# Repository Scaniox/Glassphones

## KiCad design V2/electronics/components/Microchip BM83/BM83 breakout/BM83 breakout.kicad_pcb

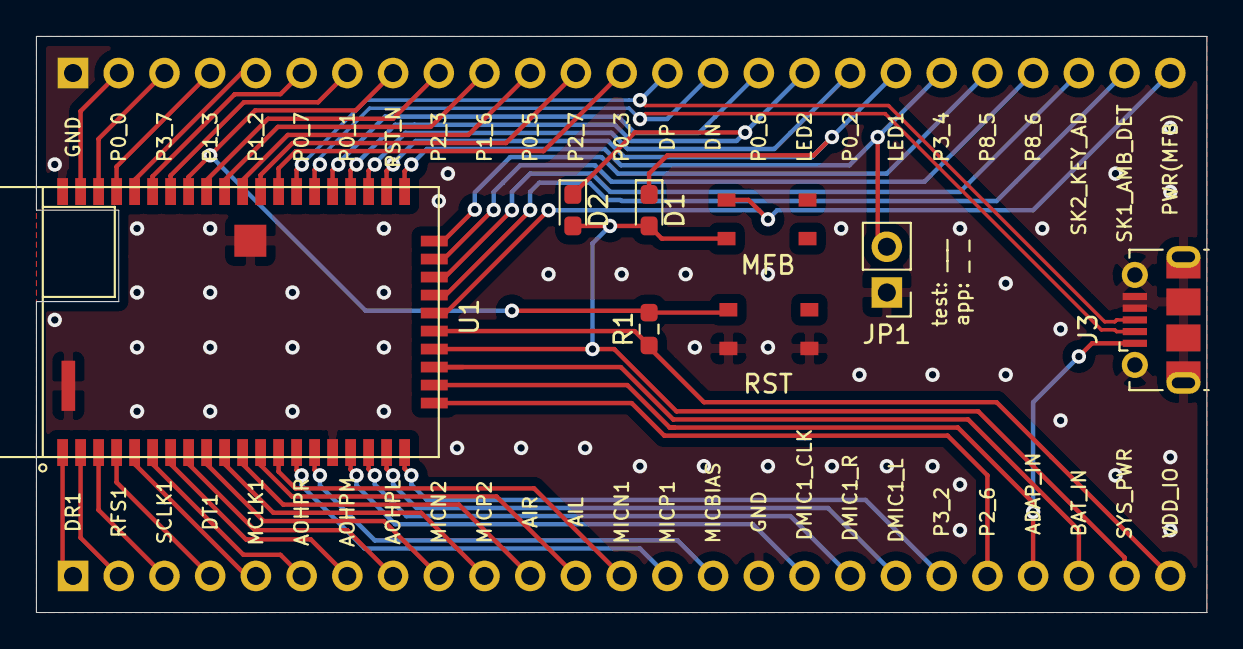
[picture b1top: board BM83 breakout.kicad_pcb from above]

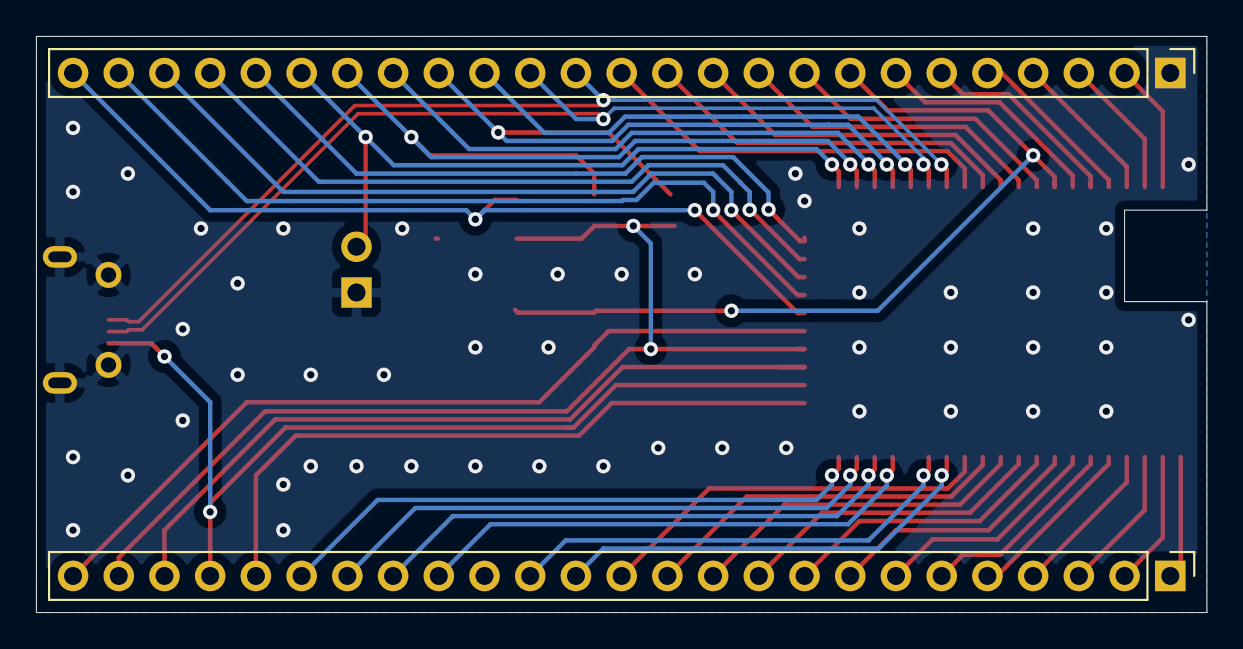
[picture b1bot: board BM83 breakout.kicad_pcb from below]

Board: 2 copper layers, 65.0 x 32.0 mm, 10 parts (2 on the bottom side), 49 nets.

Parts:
D1: LED1; LED_0603_1608Metric_Pad1.05x0.95mm_HandSolder
D2: LED2; LED_0603_1608Metric_Pad1.05x0.95mm_HandSolder
J1, J2: Conn_01x25; PinHeader_1x25_P2.54mm_Vertical
J3: USB_B_Micro; USB_Micro-B_Molex-105017-0001
JP1: Jumper_NO_Small; PinHeader_1x02_P2.54mm_Vertical
MFB: PWR MFB; TL3365_button
R1: 4R7; R_0603_1608Metric_Pad0.98x0.95mm_HandSolder
RST: RESET; TL3365_button
U1: BM83

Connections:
/ADAP_IN: J1.22, J3.1, U1.22
/AIL: J1.12, U1.12
/AIR: J1.11, U1.11
/AOHPL: J1.8, U1.8
/AOHPM: J1.7, U1.7
/AOHPR: J1.6, U1.6
/BAT_IN: J1.23, U1.23
/DMIC1_CLK: J1.17, U1.17
/DMIC1_L: J1.19, U1.19
/DMIC1_R: J1.18, U1.18
/DN: J2.15, J3.2, U1.36
/DP: J2.14, J3.3, U1.37
/DR1: J1.1, U1.1
/DT1: J1.4, U1.4
/LED1: D1.1, J2.19, U1.32
/LED2: D2.1, J2.17, U1.34
/MCLK1: J1.5, U1.5
/MICBIAS: J1.15, U1.15
/MICN1: J1.13, U1.13
/MICN2: J1.9, U1.9
/MICP1: J1.14, U1.14
/MICP2: J1.10, U1.10
/P0_0: J2.2, U1.49
/P0_1: J2.7, U1.44
/P0_2: J2.18, U1.33
/P0_3: J2.13, U1.38
/P0_5: J2.11, U1.40
/P0_6: J2.16, U1.35
/P0_7: J2.6, U1.45
/P1_2: J2.5, U1.46
/P1_3: J2.4, U1.47
/P1_6: J2.10, U1.41
/P2_3: J2.9, U1.42
/P2_6: J1.21, U1.21
/P2_7: J2.12, U1.39
/P3_2: J1.20, U1.20
/P3_4: J2.20, JP1.2, U1.31
/P3_7: J2.3, U1.48
/P8_5: J2.21, U1.30
/P8_6: J2.22, U1.29
/PWR(MFB): J2.25, MFB.1, U1.26
/RFS1: J1.2, U1.2
/RST_N: J2.8, R1.2, RST.2, U1.43
/SCLK1: J1.3, U1.3
/SK1_AMB_DET: J2.24, U1.27
/SK2_KEY_AD: J2.23, U1.28
/SYS_PWR: D1.2, D2.2, J1.24, MFB.2, U1.24
/VDD_IO: J1.25, R1.1, U1.25
GND: J1.16, J2.1, J3.4, J3.5, J3.6, JP1.1, RST.1, U1.16, U1.50

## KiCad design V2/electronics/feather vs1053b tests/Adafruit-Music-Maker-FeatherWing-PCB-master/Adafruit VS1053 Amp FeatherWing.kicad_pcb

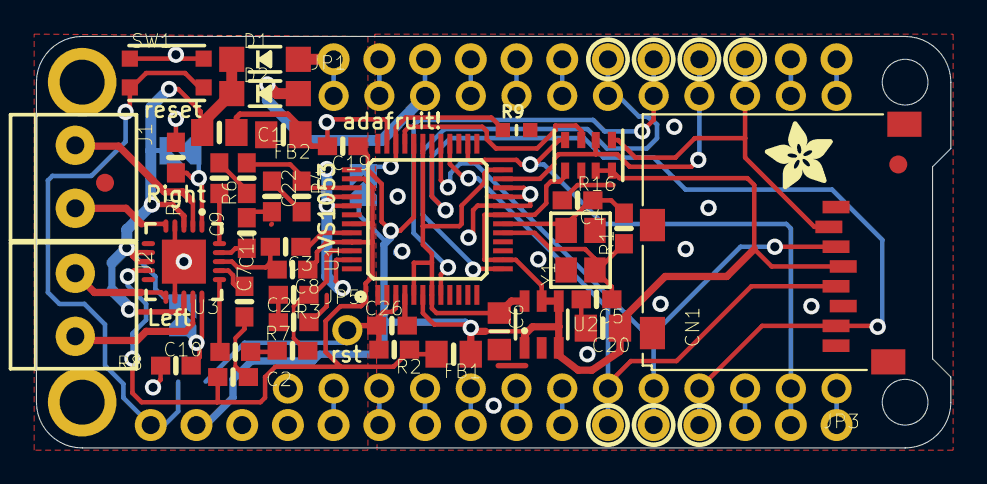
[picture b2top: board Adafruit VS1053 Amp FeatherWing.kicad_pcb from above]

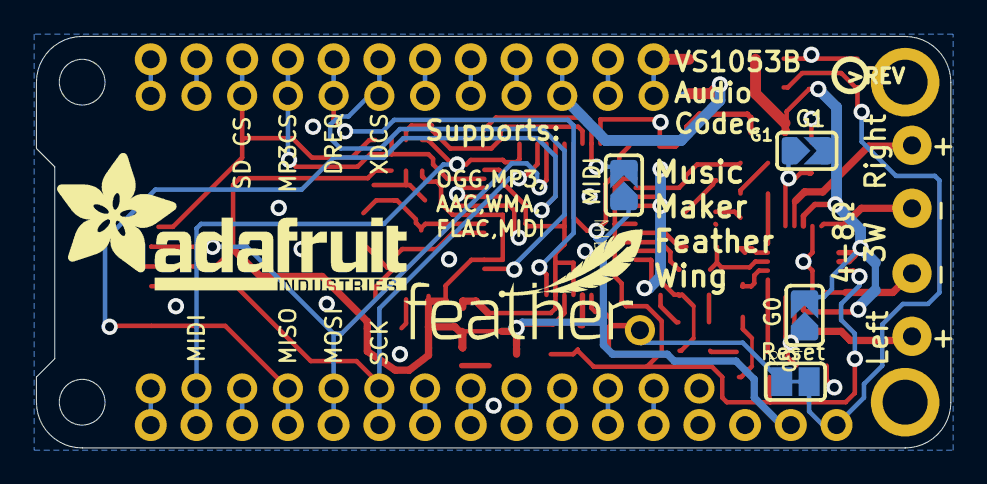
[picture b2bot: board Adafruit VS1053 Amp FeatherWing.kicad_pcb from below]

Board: 2 copper layers, 50.8 x 22.9 mm, 52 parts (7 on the bottom side), 53 nets.

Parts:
C1, C20: 10µF; 0805-NO
C2, C8, C26: 0.1µF; 0603-NO
C3: 1uF; 0603-NO
C4, C5: 22pF; 0603-NO
C6: 10µF; _0805MP
C7, C9, C10, C11, C19: 1µF; 0603-NO
C21, C22: 10nF; 0603-NO
CN1: 2908-05WB-M6; MICROSD
D1, D2: MBR120; SOD-123
FB1, FB2: FERITTE; 0805-NO
FID1, FID2: FIDUCIAL""; FIDUCIAL_1MM
G0, G1: SOLDERJUMPER_ARROW_NOPASTE
J1, J2: 3.5mm; TERMBLOCK_1X2-3.5MM
JP1: 1X12_ROUND
JP3: 1X13_ROUND_70
JP5: 1X01_ROUND
MIDI: SOLDERJUMPER_ARROW_NOPASTE
MS1: FEATHERWING_NODIM
R1: 1M; 0603-NO
R2, R5, R8: 100K; 0603-NO
R3, R4: 22; 0603-NO
R6, R7: 100; 0603-NO
R9: 100K; _0603MP
R16: 100K; RESPACK_4X0603
RST: SOLDERJUMPER_CLOSEDWIRE
SW1: KMR2; BTN_KMR2_4.6X2.8
U1: VS1053B; LQFP48
U2: AP7312-1833W6-7; SOT23-6
U3: TPA2012; WQFN20
U$36: ADAFRUIT_3.5MM
U$37: FEATHERLOGO_SMALL
U$43: PCBFEAT-REV-040
U$55: ADAFRUIT_TEXT_20MM
Y1: ABM8G-12.288MHZ-4Y-T3; CRYSTAL_3.2X2.5

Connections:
1.8V: C6.1, U1.5, U1.7, U1.24, U1.31, U2.6
3.3V: C19.1, C20.1, CN1.4, FB1.1, MIDI.1, MS1.2, R16.5, R16.7, R16.8, U1.6, U1.14, U1.19, U1.32, U2.1, U2.3, U2.4, U2.5
A: JP3.12, MS1.5
AGND: C2.2, C3.2, C7.1, C8.2, C11.1, C21.2, C22.2, FB2.2, U1.37, U1.40, U1.41, U1.47, U3.18
AVDD: C2.1, C8.1, FB1.2, R2.1, U1.38, U1.43, U1.45, U3.9
B: JP3.11, MS1.6
C: JP3.10, MS1.7
D: JP3.9, MS1.8
DREQ: JP1.8, MS1.21, U1.8
E: JP3.8, MS1.9
EN: JP1.2, MS1.27
F: JP3.7, MS1.10
G: JP3.1, MS1.16
GAIN0: G0.1, R8.1, U3.15
GAIN1: G1.1, R5.2, U3.1
GND: C1.2, C4.2, C5.2, C6.2, C19.2, C20.2, C26.2, CN1.6, CN1.MT1, CN1.MT2, FB2.1, JP3.13, MS1.4, R5.1, R8.2, R9.2, R16.6, SW1.A, SW1.A', U1.4, U1.16, U1.20, U1.21, U1.22, U1.35, U2.2, U3.4, U3.12, U3.21
GPIO0: R16.3, U1.33
GPIO1: MIDI.2, R9.1, U1.34
IN_LEFT+: C10.1, R7.1
IN_RIGHT+: C9.1, R6.1
L: JP1.6, MS1.23
LEFT: R3.1, R7.2, U1.46
M: JP1.5, MS1.24
MISO: CN1.7, JP3.4, MS1.13, U1.30
MOSI: CN1.3, JP3.5, MS1.12, U1.29
MP3CS: JP1.9, MS1.20, R16.2, U1.23
MP3RST: C26.1, JP5.1, R2.2, RST.1, U1.3
MP3_RX: JP3.2, MS1.15, R16.4, U1.26
N: JP1.4, MS1.25
unnamed: C5.1, R1.1, U1.17, Y1.1
unnamed: C4.1, R1.2, U1.18, Y1.2
unnamed: C3.1, U1.44
unnamed: C21.1, R3.2
unnamed: C22.1, R4.2
unnamed: C9.2, U3.20
unnamed: C7.2, U3.19
unnamed: C11.2, U3.17
unnamed: C10.2, U3.16
OUT_LEFT+: J1.2, U3.2
OUT_LEFT-: J1.1, U3.5
OUT_RIGHT+: J2.1, U3.14
OUT_RIGHT-: J2.2, U3.11
RIGHT: R4.1, R6.2, U1.39
SCL: JP1.11, MS1.18
SCLK: CN1.5, JP3.6, MS1.11, U1.28
SDA: JP1.12, MS1.17
SD_CS: CN1.2, JP1.10, MS1.19, R16.1
UART_RX: JP3.3, MS1.14
USB: D2.A, JP1.3, MS1.26
VBAT: D1.A, JP1.1, MS1.28
VDD: C1.1, D1.C, D2.C, G0.2, G1.2, U3.3, U3.7, U3.8, U3.13
XDCS: JP1.7, MS1.22, U1.13
~RESET: MS1.1, RST.2, SW1.B, SW1.B'

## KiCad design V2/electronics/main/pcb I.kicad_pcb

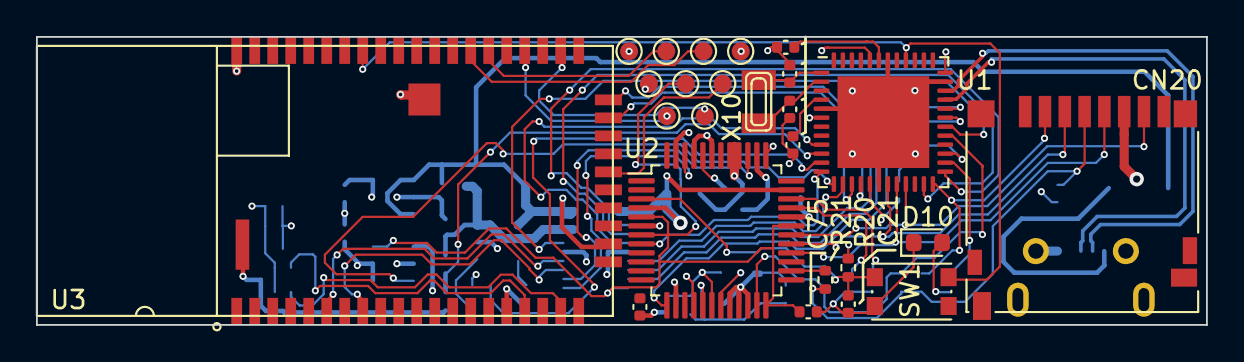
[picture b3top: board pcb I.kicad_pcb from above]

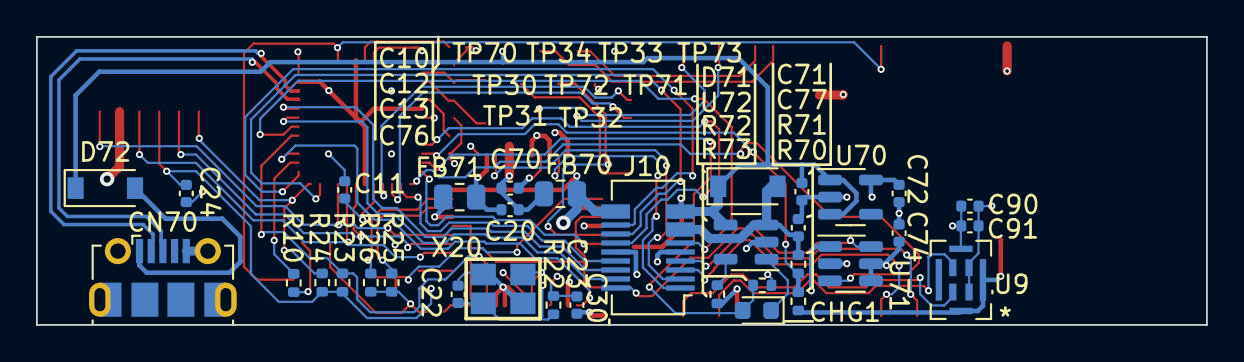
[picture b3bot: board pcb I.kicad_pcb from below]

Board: 4 copper layers, 65.0 x 16.0 mm, 59 parts (34 on the bottom side), 56 nets.

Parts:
C10, C11, C20, C24, C70, C76: 1uF; C_0402_1005Metric
C12, C13, C22, C23: 22pF; C_0402_1005Metric
C21: 0.1µF; C_0402_1005Metric
C30, C71, C72, C74, C75, C77, C90: 10uF; C_0402_1005Metric
C91: 0.1uF; C_0402_1005Metric
CHG1: ORANGE; LED_0603_1608Metric
CN20: 2908-05WB-M6; microSD_HC_Hirose_DM3D-SF
CN70: microUSB; USB_Micro-B_Molex-105017-0001
D10: RED; LED_0603_1608Metric
D71, D72: MBR120; D_SOD-123
FB70, FB71: FERITTE; R_0805_2012Metric
J10: Conn_01x20_Female; Hirose_DF12_DF12E3.0-20DP-0.5V_2x10_P0.50mm_Vertical
R10: 2.2K; R_0402_1005Metric
R20, R21, R23, R24, R25, R26, R70: 100K; R_0402_1005Metric
R22: 1M; R_0402_1005Metric
R71: 100k; R_0402_1005Metric
R72: 1K; R_0402_1005Metric
R73: 10K; R_0402_1005Metric
SW1: SPST_TACT-KMR2; SW_Push_1P1T_NO_CK_KMR2
TP30: BM83_MFB; TestPoint_Pad_D1.0mm
TP31: BM83_LED1; TestPoint_Pad_D1.0mm
TP32: BM83_LED2; TestPoint_Pad_D1.0mm
TP33: BM83_USB_DN; TestPoint_Pad_D1.0mm
TP34: BM83_USB_DP; TestPoint_Pad_D1.0mm
TP70: 5V VBUS; TestPoint_Pad_D1.0mm
TP71: 3.3V; TestPoint_Pad_D1.0mm
TP72: 1.8V; TestPoint_Pad_D1.0mm
TP73: GND; TestPoint_Pad_D1.0mm
U1: ATSAMD21G18_QFN; TQFN-48-1EP_7x7mm_P0.5mm_EP5.1x5.1mm
U2: VS1053B; LQFP-48_7x7mm_P0.5mm
U3: BM83
U9: MP34DT01TR-M
U70: SPX3819-3.3; SOT-23-5
U71: AP7312-1833W6-7; SOT-23-6
U72: MCP73831T-2ACI/OT; SOT-23-5
X10: 32.768; XTAL3215
X20: ABM8G-12.288MHZ-4Y-T3; CRYSTAL_3.2X2.5

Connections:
+1V8: C75.1, J10.11, TP72.1, U2.5 (CVDD@0), U2.7 (CVDD@1), U2.24 (CVDD@2), U2.31 (CVDD@3), U71.6 (VOUT1)
+3.3VA: C24.1, CN20.4 (SD_VDD), FB71.1, R21.2, R23.1, R24.1, U2.6 (IOVDD@0), U2.14 (IOVDD@1), U2.19 (IOVDD@2), U2.32 (XTEST), U71.1 (VOUT2)
+3V3: C11.1, C72.1, C74.1, C90.1, C91.1, J10.15, R20.1, R72.1, TP71.1, U1.6 (VDDA), U1.17 (VDDIO), U1.36 (VDDIO), U1.44 (VDDIN), U9.1 (VDD), U9.2 (LR), U70.5 (OUT), U71.4 (EN1), U71.5 (VIN)
+BATT: C77.1, D71.2 (A), J10.7, J10.8, R71.1, U72.3 (VBAT)
/A3: J10.16, U1.9 (PA04/EINT4/VREFB/AIN4/SERCOM0.0)
/A4: R70.1, R71.2, U1.10 (PA05/EINT5/AIN5/SERCOM0.1)
/AOHPL: J10.3, U3.8 (AOHPL)
/AOHPR: J10.4, U3.6 (AOHPR)
/AREF: C76.1, U1.4 (PA03/EINT3/VREFA/AIN1)
/BM83_UART_RX: U1.15 (PA10/I10/AIN18/SERCOM0+2.2/I2SCK), U3.29 (P8_6/UART_RXD)
/BM83_UART_TX: U1.16 (PA11/I11/AIN19/SERCOM0+2.3/I2SF0), U3.30 (P8_5/UART_TXD)
/CHRG_STAT: CHG1.2 (A), R72.2, U1.11 (PA06/EINT6/AIN6/SERCOM0.2)
/D2: J10.17, U1.23 (PA14/I14/SERCOM2+4.2)
/D3: J10.14, U1.14 (PA09/I2C/I9/AIN17/SERCOM0+2.1/I2SMC)
/D4: U1.13 (PA08/I2C/AIN16/SERCOM0+2.0/I2SD1), U71.3 (EN2)
/D5: CN20.2 (CS), R24.2, U1.24 (PA15/I15/SERCOM3+4.3)
/D6: R23.2, U1.29 (PA20/I4/SERCOM3+5.2/I2SSC), U2.23 (XCS)
/D7: J10.6, U1.30 (PA21/I5/SERCOM3+5.3/I2SFS0)
/D9: U1.12 (PA07/I7/AIN7/SERCOM0.3/I2SD0), U2.8 (DREQ)
/D10: U1.27 (PA18/I2/SERCOM1+3.2), U2.13 (XDCS/BSYNC)
/D11: J10.18, U1.25 (PA16/I2C/I0/SERCOM1+3.0)
/D13: R10.1, U1.26 (PA17/I2C/I1/SERCOM1+3.1)
/D+: CN70.2 (D+), U1.34 (PA25/I13/SERCOM3+5.3/D+)
/D-: CN70.3 (D-), U1.33 (PA24/I12/SERCOM3+5.2/D-)
/DMIC1_CLK: U3.17 (DMIC1_CLK), U9.3 (CLK)
/DMIC1_L: U3.19 (DMIC1_L), U9.4 (DOUT)
/DN: TP33.1, U3.36 (DM)
/DP: TP34.1, U3.37 (DP)
/GPIO0: R25.2, U2.33 (GPIO0)
/GPIO1: R26.2, U2.34 (GPIO1)
/LED1: TP31.1, U3.32 (LED1)
/LED2: TP32.1, U3.34 (LED2)
/MISO: CN20.7 (DATA_OUT), U1.21 (PA12/I12/I2C/SERCOM2+4.0), U2.30 (SO)
/MOSI: CN20.3 (DATA_IN), U1.19 (PB10/I10/SERCOM4.2/I2SMC), U2.29 (SI)
/PWR(MFB): TP30.1, U3.26 (PWR(MFB))
/SCL: J10.13, U1.32 (PA23/I2C/I7/SERCOM3+5.1/SOF)
/SCLK: CN20.5 (SCLK), U1.20 (PB11/I11/SERCOM4.3/I2SCL), U2.28 (SCLK)
/SDA: J10.12, U1.31 (PA22/I2C/I6/SERCOM3+5.0)
/vs1053_LEFT: J10.1, U2.46 (LEFT)
/vs1053_RIGHT: J10.2, U2.39 (RIGHT)
/~RESET: C21.1, R20.2, SW1.1, U1.40 (/RESET), U2.3 (XRESET), U3.43 (RST_N)
GND: C10.2, C11.2, C12.2, C13.2, C21.2, C22.2, C23.2, C24.2, C30.2, C71.2, C72.2, C74.2, C75.2, C76.2, C77.2, C90.2, C91.2, CN20.6 (GND@3), CN70.5 (GND), CN70.6 (GND), D10.1 (C), FB70.1, J10.19, J10.20, R25.1, R26.1, R70.2, R73.2, SW1.2 (S), TP73.1, U1.5 (GNDA), U1.18 (GND), U1.35 (GND), U1.42 (GND), U1.49 (GND), U2.4 (DGND@0), U2.16 (DGND@1), U2.20 (DGND@2), U2.21 (DGND@3), U2.22 (DGND@4), U2.35 (GND), U3.16 (GND), U3.50 (GND), U9.5 (GND), U9.6 (GND), U9.7 (GND), U9.8 (GND), U70.2 (GND), U71.2 (GND), U72.2 (VSS)
GNDA: C20.2, C70.2, FB70.2, J10.5, U2.37 (AGND@0), U2.40 (AGND@1), U2.41 (AGND@2), U2.47 (AGND@3)
unnamed: C10.1, U1.43 (VDDCORE)
unnamed: C12.1, U1.1 (PA00/EINT0/SERCOM1.0), X10.P$1
unnamed: C13.1, U1.2 (PA01/EINT1/SERCOM1.1), X10.P$2
unnamed: C20.1, U2.44 (RCAP)
unnamed: C22.1, R22.1, U2.17 (XTALOUT), X20.1
unnamed: C23.1, R22.2, U2.18 (XTALIN), X20.2
unnamed: CHG1.1 (C), U72.1 (STAT)
unnamed: CN70.1 (VBUS), D72.2 (A)
unnamed: D10.2 (A), R10.2
unnamed: R21.1, U2.26 (RX)
unnamed: R73.1, U72.5 (PROG)
VBUS: C30.1, C71.1, D71.1 (C), D72.1 (C), J10.9, J10.10, TP70.1, U3.22 (ADAP_IN), U70.1 (IN), U70.3 (EN), U72.4 (VDD)
VDDA: C70.1, FB71.2, U2.38 (AVDD@0), U2.43 (AVDD@1), U2.45 (AVDD@2)

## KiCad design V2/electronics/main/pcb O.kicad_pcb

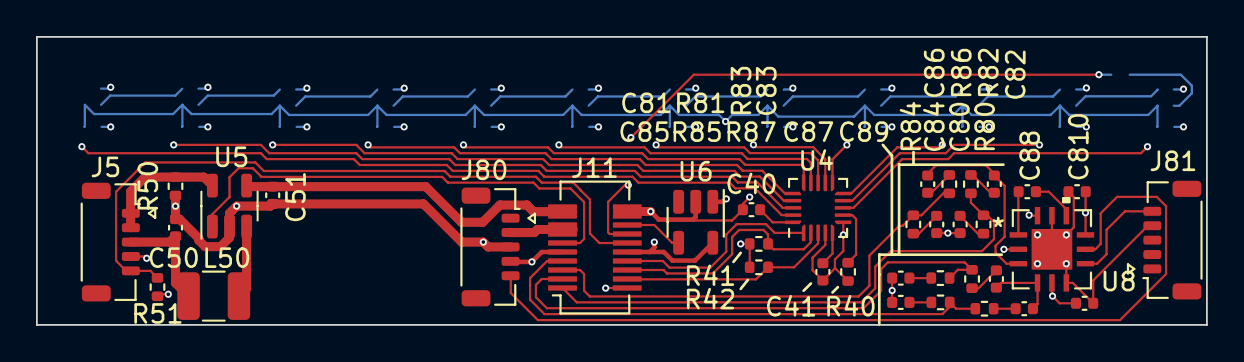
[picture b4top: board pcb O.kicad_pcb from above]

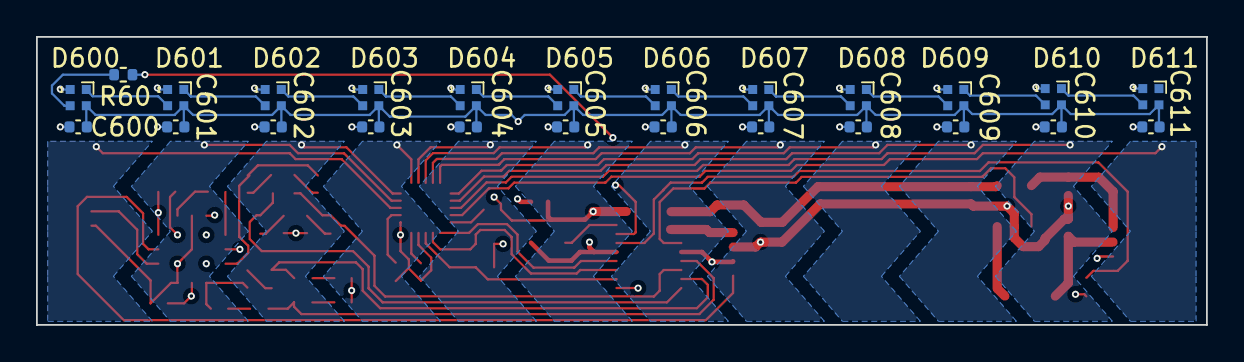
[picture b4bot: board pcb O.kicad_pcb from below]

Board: 4 copper layers, 65.0 x 16.0 mm, 62 parts (25 on the bottom side), 50 nets.

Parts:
C40, C41: 0.1uF; C_0402_1005Metric
C50, C51: 10uF; C_0402_1005Metric
C80, C81, C84, C85: 10nF; C_0402_1005Metric
C82, C83, C86, C87, C88, C89, C810: 1uf; C_0402_1005Metric
C600, C601, C602, C603, C604, C605, C606, C607, C608, C609, C610, C611: 1uF; C_0402_1005Metric
D600, D601, D602, D603, D604, D605, D606, D607, D608, D609, D610, D611: SK6812; LED_SK6812_EC15_1.5x1.5mm
J5: Conn_01x05_Female; Hirose_DF52-5S-0.8H_1x05-1MP_P0.80mm_Horizontal
J11: Conn_01x20_Male; Hirose_DF12_DF12C3.0-20DS-0.5V_2x10_P0.50mm_Vertical
J80: Conn_01x04_Female; Hirose_DF52-5S-0.8H_1x05-1MP_P0.80mm_Horizontal
J81: Conn_01x02_Female; Hirose_DF52-5S-0.8H_1x05-1MP_P0.80mm_Horizontal
L50: 4.7μH; L_1210_3225Metric
R40: 75K; R_0402_1005Metric
R41, R42: 10K; R_0402_1005Metric
R50: 0.33; R_0402_1005Metric
R51: 100K; R_0402_1005Metric
R60: 470; R_0402_1005Metric
R80, R81, R84, R85: 22; R_0402_1005Metric
R82, R83, R86, R87: 100; R_0402_1005Metric
U4: MPR121Q; UQFN-20_3x3mm_P0.4mm
U5: PAM2804; TSOT-23-5
U6: AP22814AW5; SOT-23-5
U8: max9725aetc+; max9725aetc&plus_

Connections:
+1V8: C810.1, J11.11, U8.9 (VDD), U8.12 (~SHDN)
+3V3: C40.1, J5.4, J11.15, R41.2, R42.2, U4.20 (VDD), U6.5 (IN)
+BATT: J11.7, J11.8, J80.2
/A3: J5.5, J11.16, R51.1
/AOHPL: J11.3, R84.1, R86.2
/AOHPR: J11.4, R85.1, R87.2
/D2: J11.17, R60.1
/D3: J11.14, U4.1 (#IRQ)
/D7: J11.6, U5.1 (EN)
/D11: J11.18, U6.4 (EN)
/LED_FB: J5.2, R50.1, U5.5 (FB)
/LED_SW: C50.1, J5.3, L50.2
/L_OUT: J80.5, U8.8 (OUTL)
/RGB_VDD: C600.1, C601.1, C602.1, C603.1, C604.1, C605.1, C606.1, C607.1, C608.1, C609.1, C610.1, C611.1, D600.3 (VDD), D601.3 (VDD), D602.3 (VDD), D603.3 (VDD), D604.3 (VDD), D605.3 (VDD), D606.3 (VDD), D607.3 (VDD), D608.3 (VDD), D609.3 (VDD), D610.3 (VDD), D611.3 (VDD), U6.1 (OUT)
/R_OUT: J81.5, U8.7 (OUTR)
/SCL: J11.13, R41.1, U4.2 (SCL)
/SDA: J11.12, R42.1, U4.3 (SDA)
/vs1053_LEFT: J11.1, R80.1, R82.2
/vs1053_RIGHT: J11.2, R81.1, R83.2
GND: C40.2, C41.2, C50.2, C51.1, C600.2, C601.2, C602.2, C603.2, C604.2, C605.2, C606.2, C607.2, C608.2, C609.2, C610.2, C611.2, D600.1 (VSS), D601.1 (VSS), D602.1 (VSS), D603.1 (VSS), D604.1 (VSS), D605.1 (VSS), D606.1 (VSS), D607.1 (VSS), D608.1 (VSS), D609.1 (VSS), D610.1 (VSS), D611.1 (VSS), J11.19, J11.20, J80.3, R40.1, R50.2, R51.2, U4.4 (ADDR), U4.6 (VSS), U5.2 (GND), U6.2 (GND)
GNDA: C80.2, C81.2, C84.2, C85.2, C89.2, C810.2, J11.5, J80.4, J81.4, U8.6 (SGND), U8.11 (PGND), U8.13 (EP)
unnamed: C41.1, U4.5 (VREG)
unnamed: C80.1, R80.2
unnamed: C81.1, R81.2
unnamed: C82.1, R82.1
unnamed: C82.2, C86.2, U8.3 (INL)
unnamed: C83.1, C87.2, U8.4 (INR)
unnamed: C83.2, R83.1
unnamed: C84.1, R84.2
unnamed: C85.1, R85.2
unnamed: C86.1, R86.1
unnamed: C87.1, R87.1
unnamed: C88.1, U8.1 (C1N)
unnamed: C88.2, U8.10 (C1P)
unnamed: C89.1, U8.2 (PVSS), U8.5 (VSS)
unnamed: D600.2 (DIN), R60.2
unnamed: D600.4 (DOUT), D601.2 (DIN)
unnamed: D601.4 (DOUT), D602.2 (DIN)
unnamed: D602.4 (DOUT), D603.2 (DIN)
unnamed: D603.4 (DOUT), D604.2 (DIN)
unnamed: D604.4 (DOUT), D605.2 (DIN)
unnamed: D605.4 (DOUT), D606.2 (DIN)
unnamed: D606.4 (DOUT), D607.2 (DIN)
unnamed: D607.4 (DOUT), D608.2 (DIN)
unnamed: D608.4 (DOUT), D609.2 (DIN)
unnamed: D609.4 (DOUT), D610.2 (DIN)
unnamed: D610.4 (DOUT), D611.2 (DIN)
unnamed: L50.1, U5.3 (SW)
unnamed: R40.2, U4.7 (REXT)
VBUS: C51.2, J11.9, J11.10, U5.4 (VIN)

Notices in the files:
parts and their libraries:
Copyright 2021 Accelerated Designs. All rights reserved.
